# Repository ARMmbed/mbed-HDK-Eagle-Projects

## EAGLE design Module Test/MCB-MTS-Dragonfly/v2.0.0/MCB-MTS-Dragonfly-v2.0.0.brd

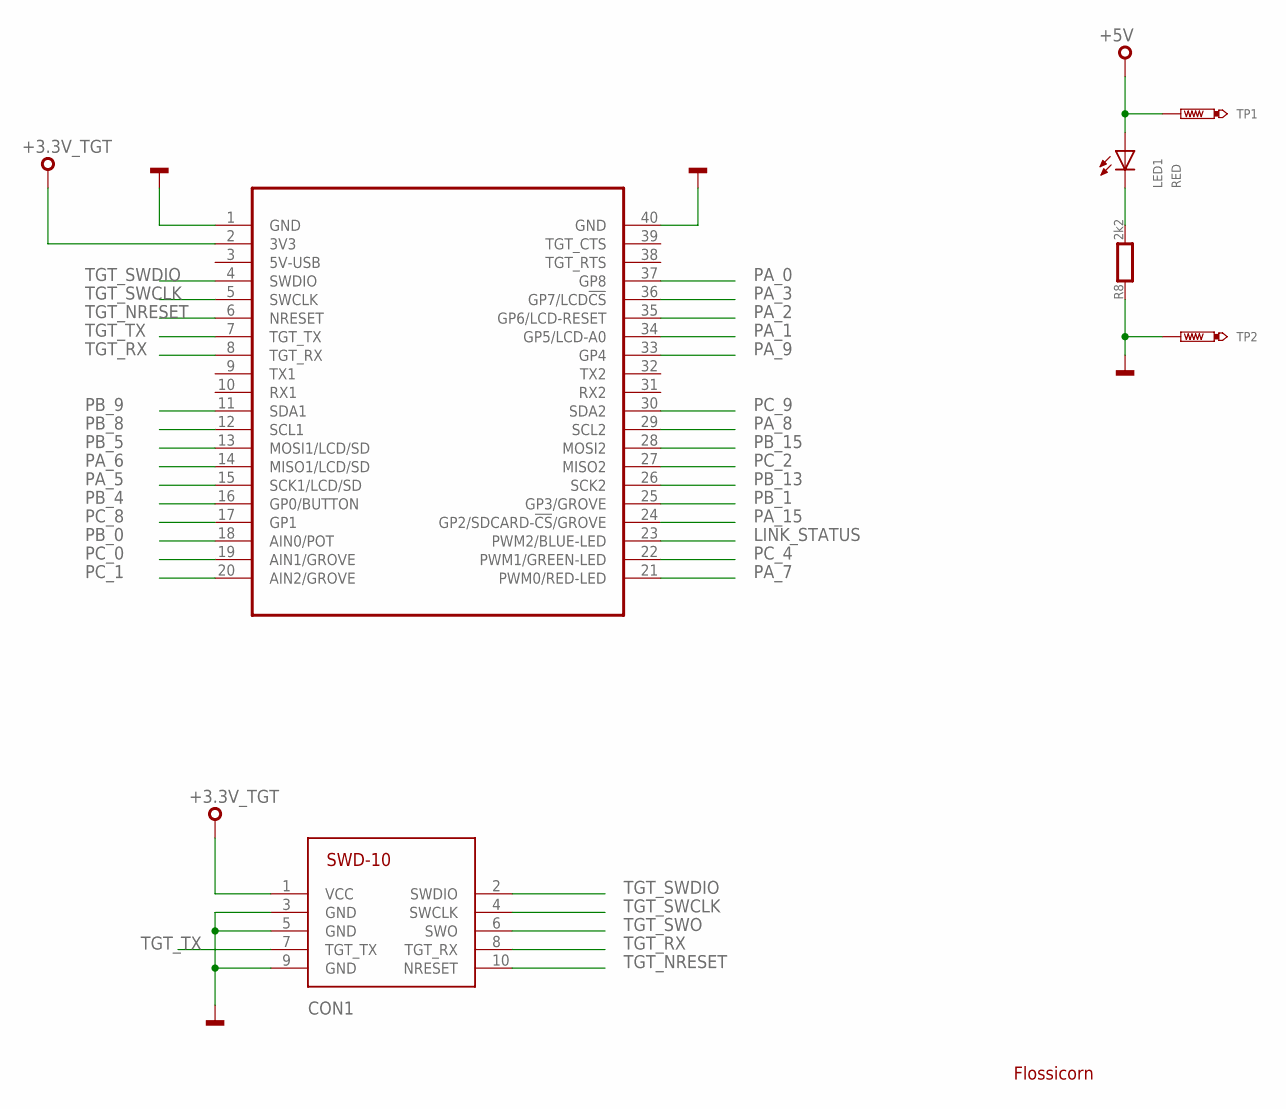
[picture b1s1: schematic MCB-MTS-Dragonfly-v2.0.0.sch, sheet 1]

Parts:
CON1: SWD-10/TC2050_SMD; FTSH-105-02
LED1: RED; CHIPLED_0603
MOD2: MODULE_DAUGHTER
R8: 2k2; 0603
SS1: FLOSSICORN0.5; FLOSSICORN-0.5
TP1, TP2: TEST-POINT-50R-PTH; TP50-PTH

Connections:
+3.3V_TGT: CON1.1 (VCC), MOD2.2 (3V3)
+5V: LED1.A, TP1.TP; also elsewhere on the board
GND: CON1.3 (GND), CON1.5 (GND), CON1.9 (GND), MOD2.1 (GND), MOD2.40 (GND), R8.1, TP2.TP; also elsewhere on the board
LINK_STATUS: MOD2.23 (PWM2/BLUE-LED); also elsewhere on the board
unnamed: LED1.C, R8.2
PA_0: MOD2.37 (GP8); also elsewhere on the board
PA_1: MOD2.34 (GP5/LCD-A0); also elsewhere on the board
PA_2: MOD2.35 (GP6/LCD-RESET); also elsewhere on the board
PA_3: MOD2.36 (GP7/LCD!CS); also elsewhere on the board
PA_5: MOD2.15 (SCK1/LCD/SD); also elsewhere on the board
PA_6: MOD2.14 (MISO1/LCD/SD); also elsewhere on the board
PA_7: MOD2.21 (PWM0/RED-LED); also elsewhere on the board
PA_8: MOD2.29 (SCL2); also elsewhere on the board
PA_9: MOD2.33 (GP4); also elsewhere on the board
PA_15: MOD2.24 (GP2/SDCARD-!CS!/GROVE); also elsewhere on the board
PB_0: MOD2.18 (AIN0/POT); also elsewhere on the board
PB_1: MOD2.25 (GP3/GROVE); also elsewhere on the board
PB_4: MOD2.16 (GP0/BUTTON); also elsewhere on the board
PB_5: MOD2.13 (MOSI1/LCD/SD); also elsewhere on the board
PB_8: MOD2.12 (SCL1); also elsewhere on the board
PB_9: MOD2.11 (SDA1); also elsewhere on the board
PB_13: MOD2.26 (SCK2); also elsewhere on the board
PB_15: MOD2.28 (MOSI2); also elsewhere on the board
PC_0: MOD2.19 (AIN1/GROVE); also elsewhere on the board
PC_1: MOD2.20 (AIN2/GROVE); also elsewhere on the board
PC_2: MOD2.27 (MISO2); also elsewhere on the board
PC_4: MOD2.22 (PWM1/GREEN-LED); also elsewhere on the board
PC_8: MOD2.17 (GP1); also elsewhere on the board
PC_9: MOD2.30 (SDA2); also elsewhere on the board
TGT_NRESET: CON1.10 (NRESET), MOD2.6 (NRESET); also elsewhere on the board
TGT_RX: CON1.8 (TGT_RX), MOD2.8 (TGT_RX); also elsewhere on the board
TGT_SWCLK: CON1.4 (SWCLK), MOD2.5 (SWCLK); also elsewhere on the board
TGT_SWDIO: CON1.2 (SWDIO), MOD2.4 (SWDIO); also elsewhere on the board
TGT_SWO: CON1.6 (SWO); also elsewhere on the board
TGT_TX: CON1.7 (TGT_TX), MOD2.7 (TGT_TX); also elsewhere on the board

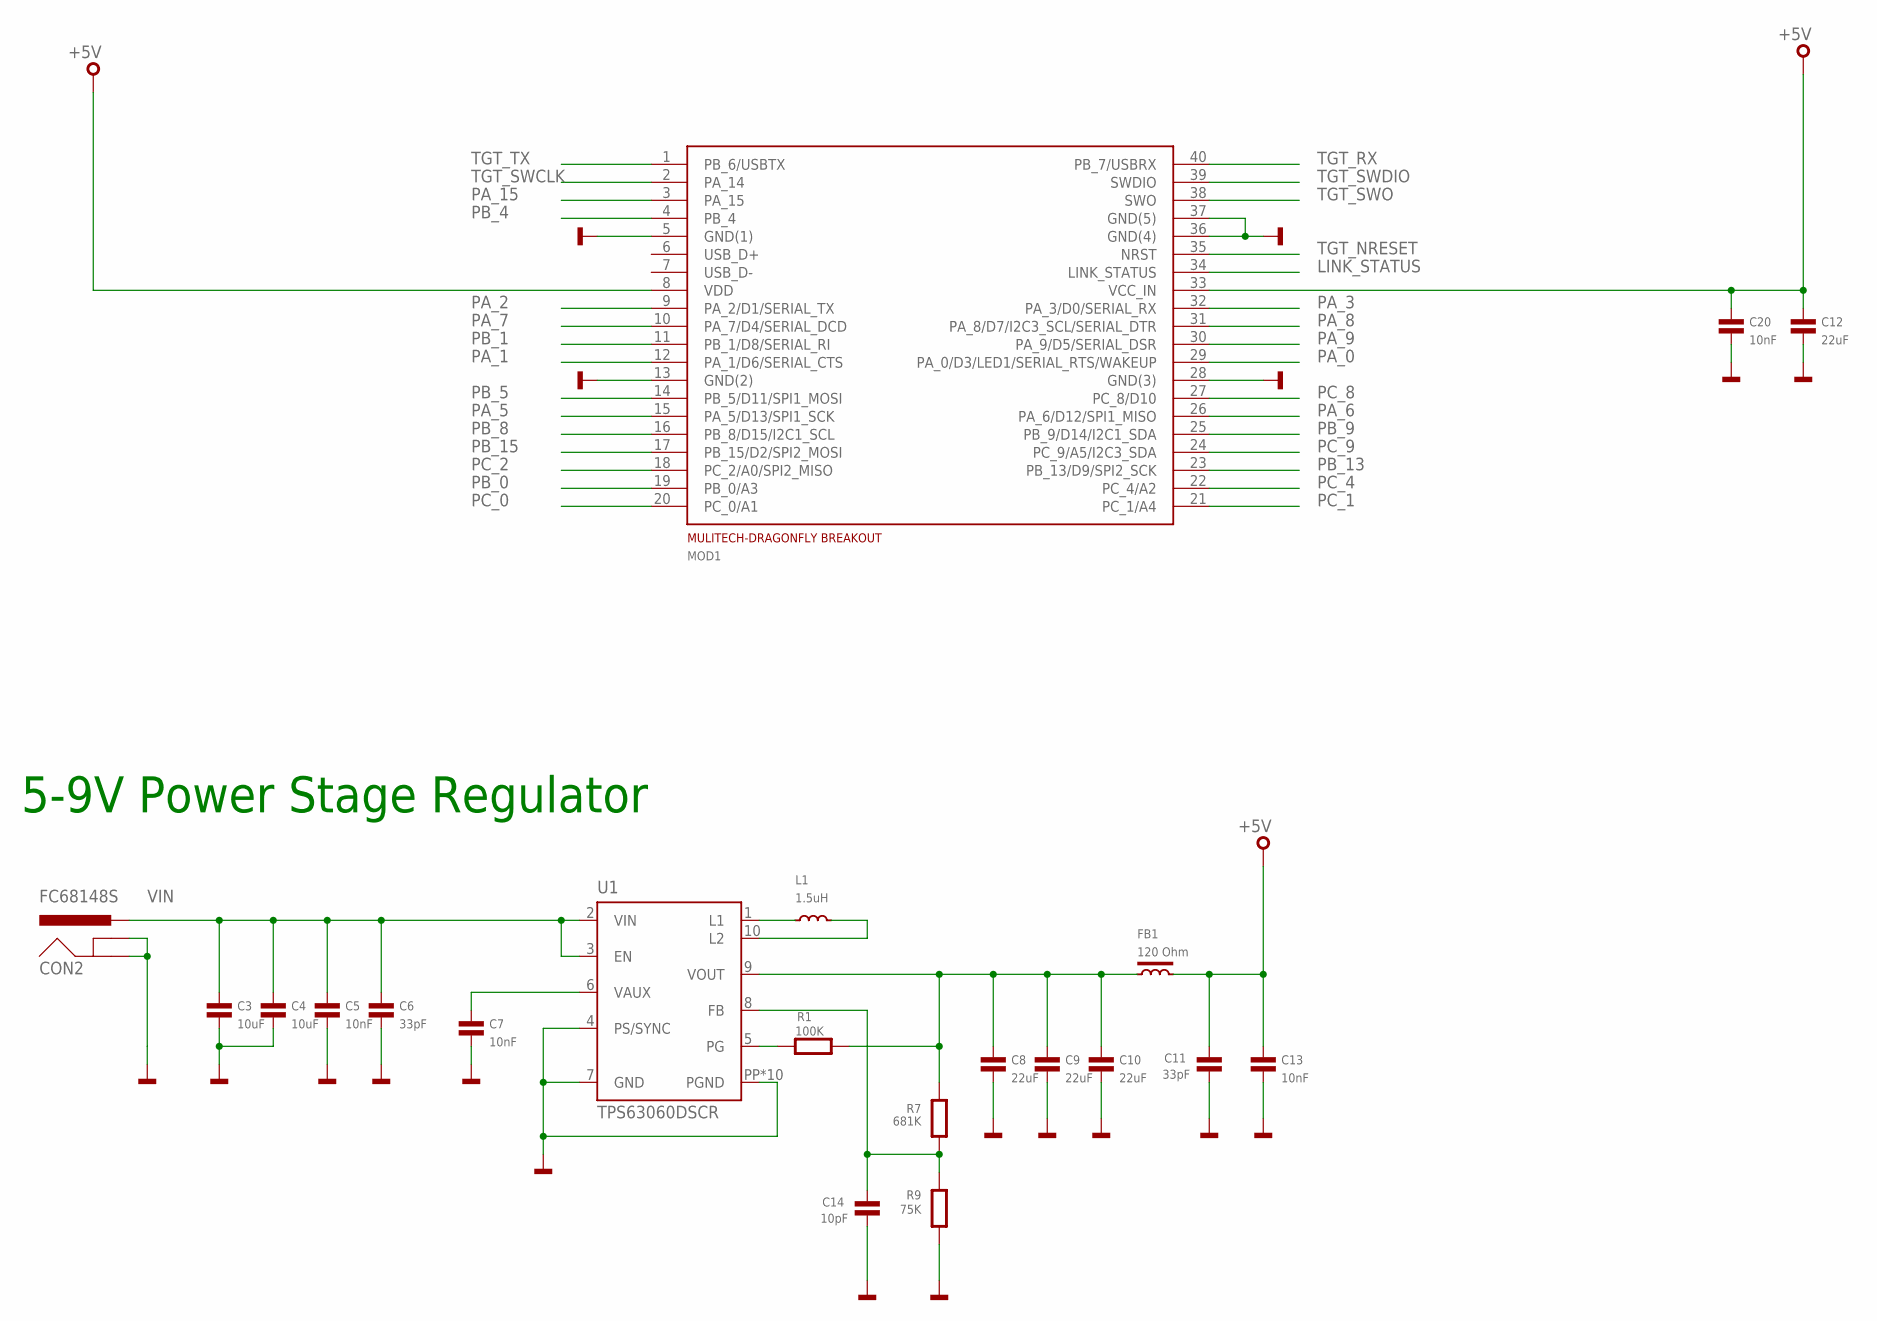
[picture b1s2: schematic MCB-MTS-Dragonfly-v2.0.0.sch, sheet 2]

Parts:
C3, C4: 10uF; 0603
C5, C7, C13, C20: 10nF; 0603
C6, C11: 33pF; 0603
C8, C9, C10, C12: 22uF; 0603
C14: 10pF; 0603
CON2: FC68148S
FB1: 120 Ohm; 0603
L1: 1.5uH; XFL4020-472MEC
MOD1: MULITECH-DRAGONFLY-BREAKOUT
R1: 100K; 0402
R7: 681K; 0402
R9: 75K; 0402
U1: TPS63060DSCR; DSC-S-PWSON-N10

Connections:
+5V: C11.1, C12.1, C13.1, C20.1, FB1.2, MOD1.8 (VDD), MOD1.33 (VCC_IN); also elsewhere on the board
GND: C3.2, C4.2, C5.2, C6.2, C7.2, C8.2, C9.2, C10.2, C11.2, C12.2, C13.2, C14.2, C20.2, CON2.2 (GNDBREAK), CON2.3 (GND), MOD1.5 (GND(1)), MOD1.13 (GND(2)), MOD1.28 (GND(3)), MOD1.36 (GND(4)), MOD1.37 (GND(5)), R9.1, U1.4 (PS/SYNC), U1.7 (GND), U1.PP (PGND), U1.PP@1 (PGND), U1.PP@2 (PGND), U1.PP@3 (PGND), U1.PP@4 (PGND), U1.PP@5 (PGND), U1.PP@7 (PGND), U1.PP@8 (PGND), U1.PP@9 (PGND), U1.PP@10 (PGND); also elsewhere on the board
LINK_STATUS: MOD1.34 (LINK_STATUS); also elsewhere on the board
unnamed: C7.1, U1.6 (VAUX)
unnamed: L1.P$1, U1.1 (L1)
unnamed: L1.P$2, U1.10 (L2)
unnamed: C14.1, R7.1, R9.2, U1.8 (FB)
unnamed: C8.1, C9.1, C10.1, FB1.1, R1.2, R7.2, U1.9 (VOUT)
unnamed: R1.1, U1.5 (PG)
PA_0: MOD1.29 (PA_0/D3/LED1/SERIAL_RTS/WAKEUP); also elsewhere on the board
PA_1: MOD1.12 (PA_1/D6/SERIAL_CTS); also elsewhere on the board
PA_2: MOD1.9 (PA_2/D1/SERIAL_TX); also elsewhere on the board
PA_3: MOD1.32 (PA_3/D0/SERIAL_RX); also elsewhere on the board
PA_5: MOD1.15 (PA_5/D13/SPI1_SCK); also elsewhere on the board
PA_6: MOD1.26 (PA_6/D12/SPI1_MISO); also elsewhere on the board
PA_7: MOD1.10 (PA_7/D4/SERIAL_DCD); also elsewhere on the board
PA_8: MOD1.31 (PA_8/D7/I2C3_SCL/SERIAL_DTR); also elsewhere on the board
PA_9: MOD1.30 (PA_9/D5/SERIAL_DSR); also elsewhere on the board
PA_15: MOD1.3 (PA_15); also elsewhere on the board
PB_0: MOD1.19 (PB_0/A3); also elsewhere on the board
PB_1: MOD1.11 (PB_1/D8/SERIAL_RI); also elsewhere on the board
PB_4: MOD1.4 (PB_4); also elsewhere on the board
PB_5: MOD1.14 (PB_5/D11/SPI1_MOSI); also elsewhere on the board
PB_8: MOD1.16 (PB_8/D15/I2C1_SCL); also elsewhere on the board
PB_9: MOD1.25 (PB_9/D14/I2C1_SDA); also elsewhere on the board
PB_13: MOD1.23 (PB_13/D9/SPI2_SCK); also elsewhere on the board
PB_15: MOD1.17 (PB_15/D2/SPI2_MOSI); also elsewhere on the board
PC_0: MOD1.20 (PC_0/A1); also elsewhere on the board
PC_1: MOD1.21 (PC_1/A4); also elsewhere on the board
PC_2: MOD1.18 (PC_2/A0/SPI2_MISO); also elsewhere on the board
PC_4: MOD1.22 (PC_4/A2); also elsewhere on the board
PC_8: MOD1.27 (PC_8/D10); also elsewhere on the board
PC_9: MOD1.24 (PC_9/A5/I2C3_SDA); also elsewhere on the board
TGT_NRESET: MOD1.35 (NRST); also elsewhere on the board
TGT_RX: MOD1.40 (PB_7/USBRX); also elsewhere on the board
TGT_SWCLK: MOD1.2 (PA_14); also elsewhere on the board
TGT_SWDIO: MOD1.39 (SWDIO); also elsewhere on the board
TGT_SWO: MOD1.38 (SWO); also elsewhere on the board
TGT_TX: MOD1.1 (PB_6/USBTX); also elsewhere on the board
VIN: C3.1, C4.1, C5.1, C6.1, CON2.1-1 (PWR), CON2.1-2 (PWR), U1.2 (VIN), U1.3 (EN)

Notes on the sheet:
5-9V Power Stage Regulator

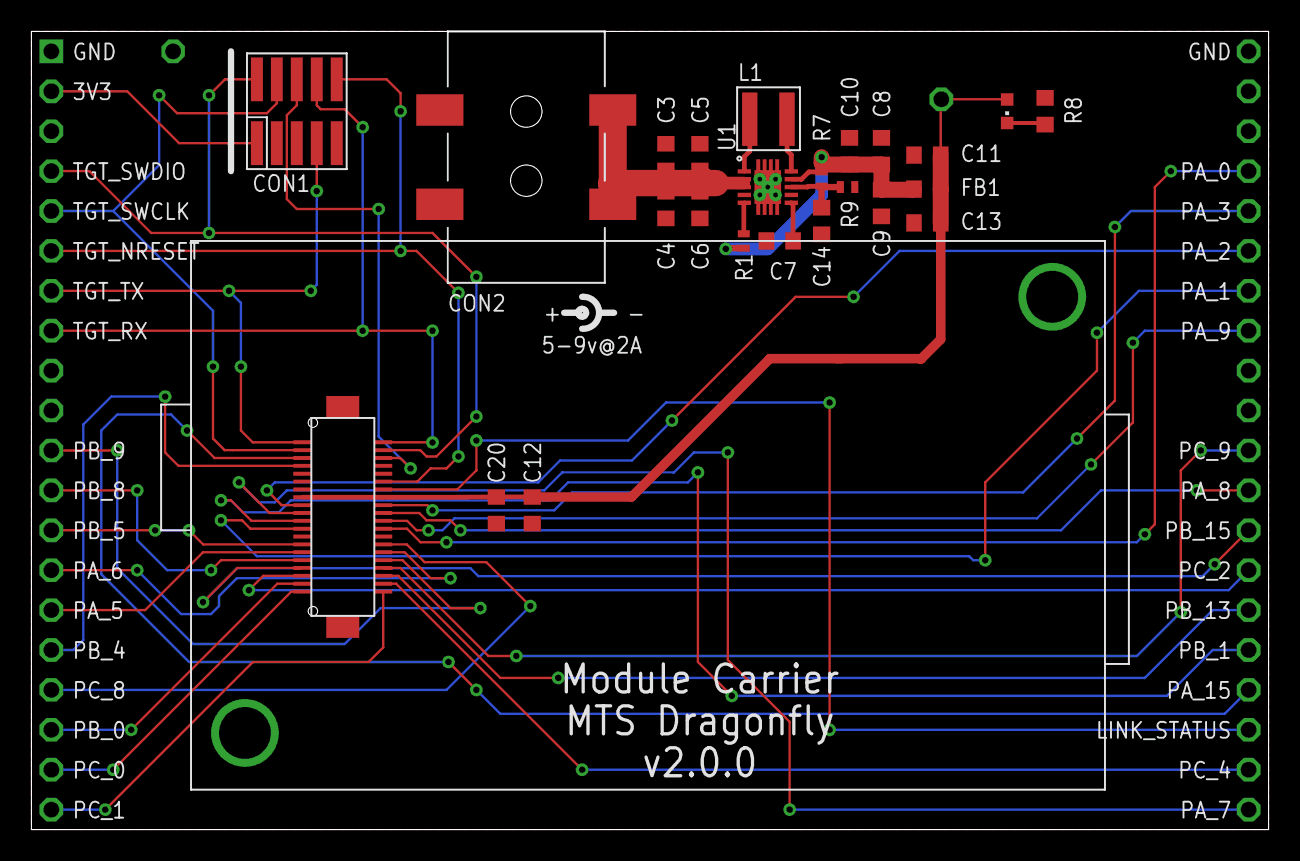
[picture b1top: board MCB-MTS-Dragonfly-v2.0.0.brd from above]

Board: 2 copper layers, 78.7 x 50.8 mm, 28 parts (0 on the bottom side), 42 nets.

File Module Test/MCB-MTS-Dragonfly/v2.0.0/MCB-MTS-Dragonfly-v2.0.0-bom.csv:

"Qty";"Value";"Device";"Package";"Parts";"Description";"MF";"MFN";"OC-DIGIKEY";"OC-MOUSER";"OC-NEWARK";
"1";"1.5uH";"INDUCTORXFL4020";"XFL4020-472MEC";"L1";"Inductor";"";"";"";"";"";
"1";"100K";"RESISTOR0402";"0402";"R1";"Resistor";"";"";"";"";"";
"4";"10nF";"CAPACITOR0603";"0603";"C5, C7, C13, C20";"Capacitor";"";"";"";"";"";
"1";"10pF";"CAPACITOR0603";"0603";"C14";"Capacitor";"";"";"";"";"";
"2";"10uF";"CAPACITOR0603";"0603";"C3, C4";"Capacitor";"";"";"";"";"";
"1";"120 Ohm";"FERRITE0603";"0603";"FB1";"Ferrite Bead";"";"";"";"";"";
"4";"22uF";"CAPACITOR0603";"0603";"C8, C9, C10, C12";"Capacitor";"";"";"";"";"";
"1";"2k2";"RESISTOR0603";"0603";"R8";"Resistor";"";"";"";"";"";
"2";"33pF";"CAPACITOR0603";"0603";"C6, C11";"Capacitor";"";"";"";"";"";
"1";"681K";"RESISTOR0402";"0402";"R7";"Resistor";"";"";"";"";"";
"1";"75K";"RESISTOR0402";"0402";"R9";"Resistor";"";"";"";"";"";
"1";"FC68148S";"FC68148S";"FC68148S";"CON2";"Power Jack";"";"";"";"";"";
"1";"FLOSSICORN0.5";"FLOSSICORN0.5";"FLOSSICORN-0.5";"SS1";"";"";"";"";"";"";
"1";"MODULE_DAUGHTER";"MODULE_DAUGHTER";"MODULE_DAUGHTER";"MOD2";"";"";"";"";"";"";
"1";"MULITECH-DRAGONFLY-BREAKOUT";"MULITECH-DRAGONFLY-BREAKOUT";"MULITECH-DRAGONFLY-BREAKOUT";"MOD1";"Breakout for Multitech Dragonfly";"Hirose";"DF17(2.0)-40DP-0.5V(57)";"H11130CT-ND";"798-DF172040DP05V57";"2300341";
"1";"RED";"SMD_LED0603";"CHIPLED_0603";"LED1";"LED SMD, Colour Red";"Wurth Electronics Inc";"150060RS75000";"732-4978-1-ND";"710-150060RS75000";"2322071";
"1";"SWD-10/TC2050_SMD";"SWD-10/TC2050_SMD";"FTSH-105-02";"CON1";"1mm pitch 10-Pin Cortex Programming Header with optional TC2050 footprint solderless interchangeable";"";"";"";"";"";
"2";"TEST-POINT-50R-PTH";"TEST-POINT-50R-PTH";"TP50-PTH";"TP1, TP2";"";"";"";"";"";"";
"1";"TPS63060DSCR";"TPS63060DSCR";"DSC-S-PWSON-N10";"U1";"Buck Boost Conveter (2.5V-12Vin, 2.5V-8Vout, 2Aout)";"TEXAS INSTRUMENTS";"TPS63060DSCR";"296-30204-1-ND";"595-TPS63060DSCR";"76T8143";

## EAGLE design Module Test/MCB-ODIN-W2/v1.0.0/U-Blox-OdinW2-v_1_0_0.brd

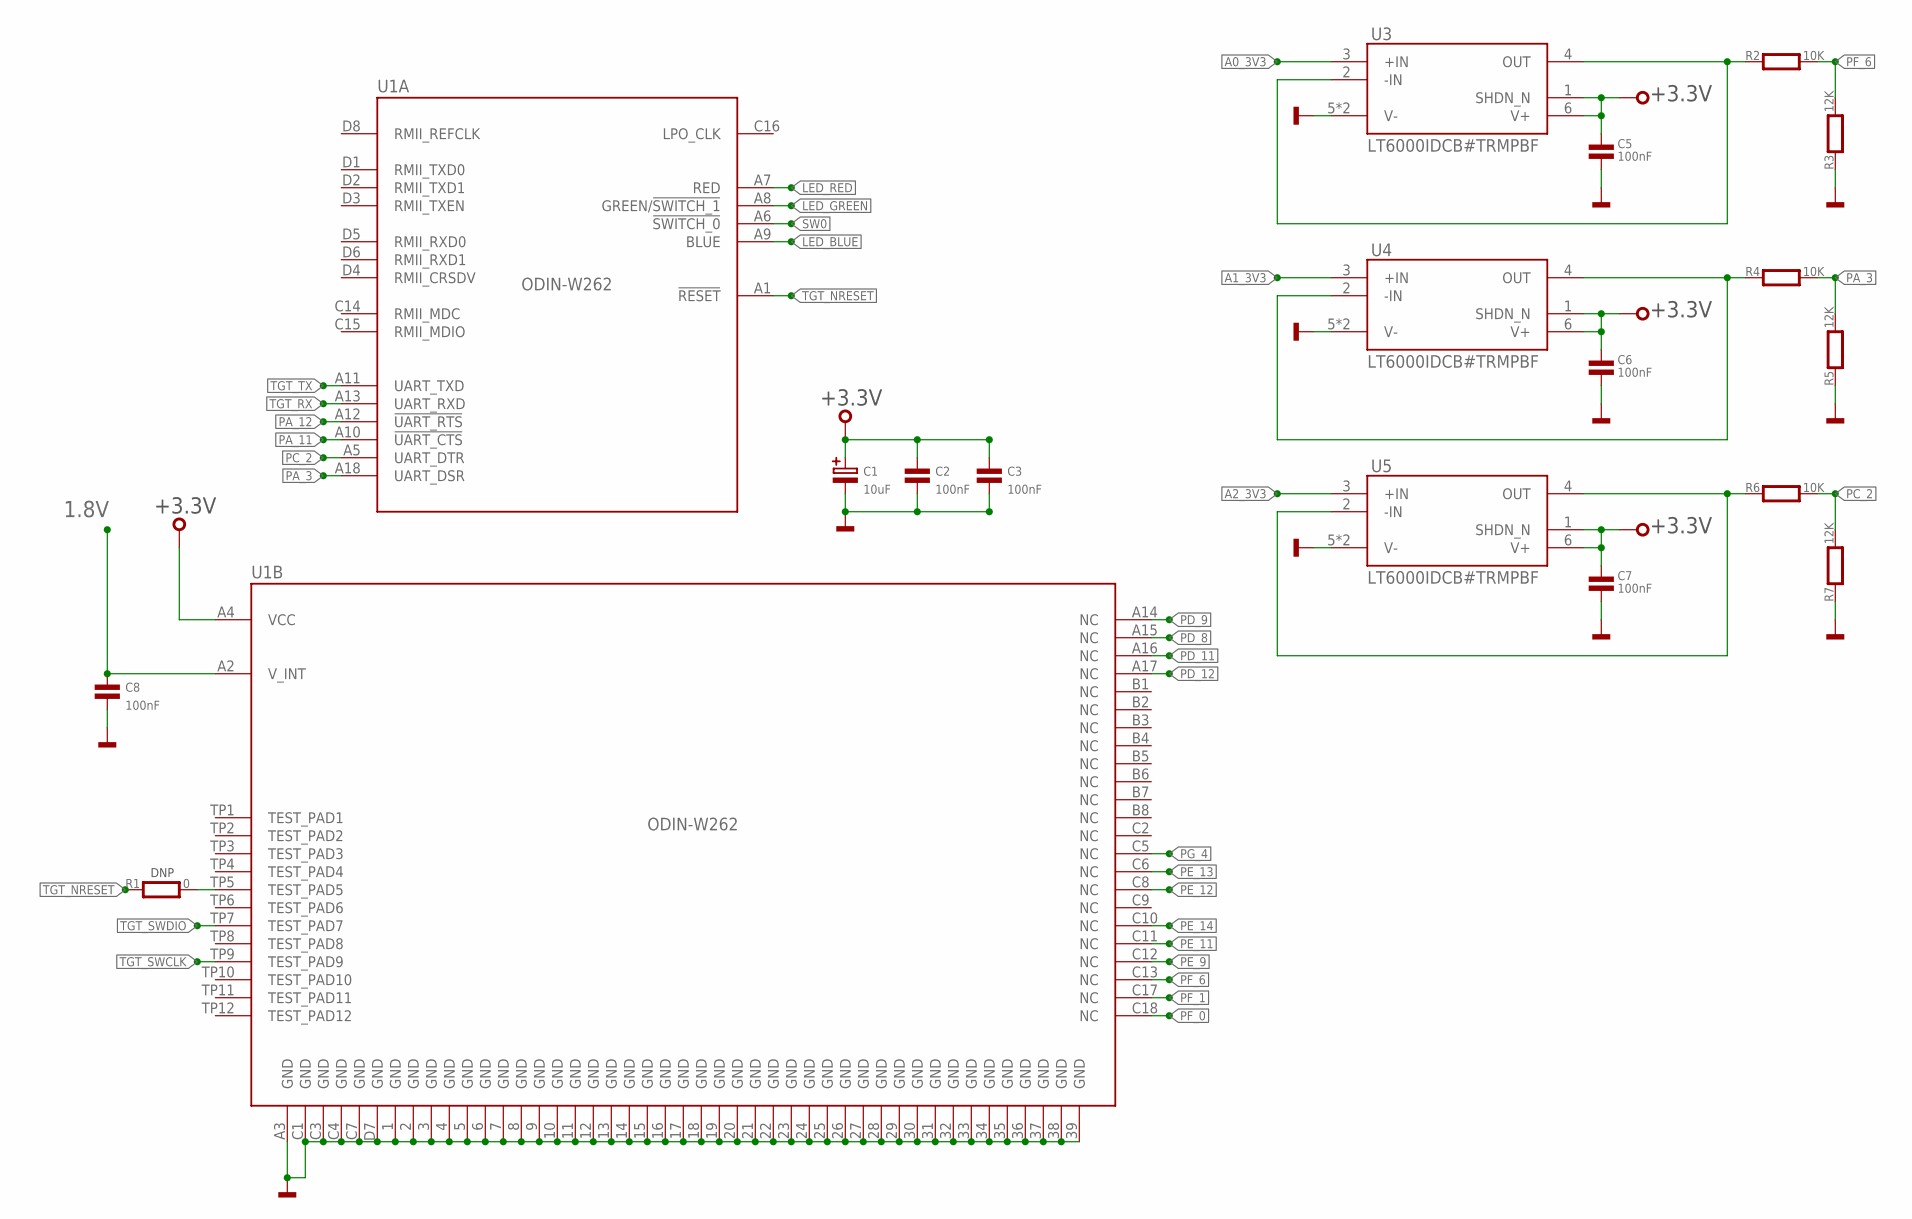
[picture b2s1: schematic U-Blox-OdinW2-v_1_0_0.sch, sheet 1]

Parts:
C1: 10uF; SMC_B
C2, C3, C5, C6, C7, C8: 100nF; 0603
R1: 0; 0402
R2, R4, R6: 10K; 0402
R3, R5, R7: 12K; 0402
U1: ODIN-W262; ODIN-88
U3, U4, U5: LT6000IDCB#TRMPBF; 6-DFN

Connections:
1.8V: C8.1, U1.A2 (V_INT); also elsewhere on the board
+3.3V: C1.+, C2.1, C3.1, C5.1, C6.1, C7.1, U1.A4 (VCC), U3.1 (SHDN_N), U3.6 (V+), U4.1 (SHDN_N), U4.6 (V+), U5.1 (SHDN_N), U5.6 (V+); also elsewhere on the board
A0_3V3: U3.3 (+IN); also elsewhere on the board
A1_3V3: U4.3 (+IN); also elsewhere on the board
A2_3V3: U5.3 (+IN); also elsewhere on the board
GND: C1.-, C2.2, C3.2, C5.2, C6.2, C7.2, C8.2, R3.1, R5.1, R7.1, U1.1 (GND), U1.2 (GND), U1.3 (GND), U1.4 (GND), U1.5 (GND), U1.6 (GND), U1.7 (GND), U1.8 (GND), U1.9 (GND), U1.10 (GND), U1.11 (GND), U1.12 (GND), U1.13 (GND), U1.14 (GND), U1.15 (GND), U1.16 (GND), U1.17 (GND), U1.18 (GND), U1.19 (GND), U1.20 (GND), U1.21 (GND), U1.22 (GND), U1.23 (GND), U1.24 (GND), U1.25 (GND), U1.26 (GND), U1.27 (GND), U1.28 (GND), U1.29 (GND), U1.30 (GND), U1.31 (GND), U1.32 (GND), U1.33 (GND), U1.34 (GND), U1.35 (GND), U1.36 (GND), U1.37 (GND), U1.38 (GND), U1.39 (GND), U1.A3 (GND), U1.C1 (GND), U1.C3 (GND), U1.C4 (GND), U1.C7 (GND), U1.D7 (GND), U3.5 (V-), U3.P$7 (V-), U4.5 (V-), U4.P$7 (V-), U5.5 (V-), U5.P$7 (V-); also elsewhere on the board
LED_BLUE: U1.A9 (BLUE); also elsewhere on the board
LED_GREEN: U1.A8 (GREEN/!SWITCH_1); also elsewhere on the board
LED_RED: U1.A7 (RED); also elsewhere on the board
unnamed: R1.2, U1.TP5 (TEST_PAD5)
unnamed: R2.1, U3.2 (-IN), U3.4 (OUT)
unnamed: R4.1, U4.2 (-IN), U4.4 (OUT)
unnamed: R6.1, U5.2 (-IN), U5.4 (OUT)
PA_3: R4.2, R5.2, U1.A18 (UART_DSR)
PA_11: U1.A10 (!UART_CTS); also elsewhere on the board
PA_12: U1.A12 (!UART_RTS); also elsewhere on the board
PC_2: R6.2, R7.2, U1.A5 (UART_DTR)
PD_8: U1.A15 (NC); also elsewhere on the board
PD_9: U1.A14 (NC); also elsewhere on the board
PD_11: U1.A16 (NC); also elsewhere on the board
PD_12: U1.A17 (NC); also elsewhere on the board
PE_9: U1.C12 (NC); also elsewhere on the board
PE_11: U1.C11 (NC); also elsewhere on the board
PE_12: U1.C8 (NC); also elsewhere on the board
PE_13: U1.C6 (NC); also elsewhere on the board
PE_14: U1.C10 (NC); also elsewhere on the board
PF_0: U1.C18 (NC); also elsewhere on the board
PF_1: U1.C17 (NC); also elsewhere on the board
PF_6: R2.2, R3.2, U1.C13 (NC)
PG_4: U1.C5 (NC); also elsewhere on the board
SW0: U1.A6 (!SWITCH_0); also elsewhere on the board
TGT_NRESET: R1.1, U1.A1 (!RESET); also elsewhere on the board
TGT_RX: U1.A13 (UART_RXD); also elsewhere on the board
TGT_SWCLK: U1.TP9 (TEST_PAD9); also elsewhere on the board
TGT_SWDIO: U1.TP7 (TEST_PAD7); also elsewhere on the board
TGT_TX: U1.A11 (UART_TXD); also elsewhere on the board

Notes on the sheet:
DNP

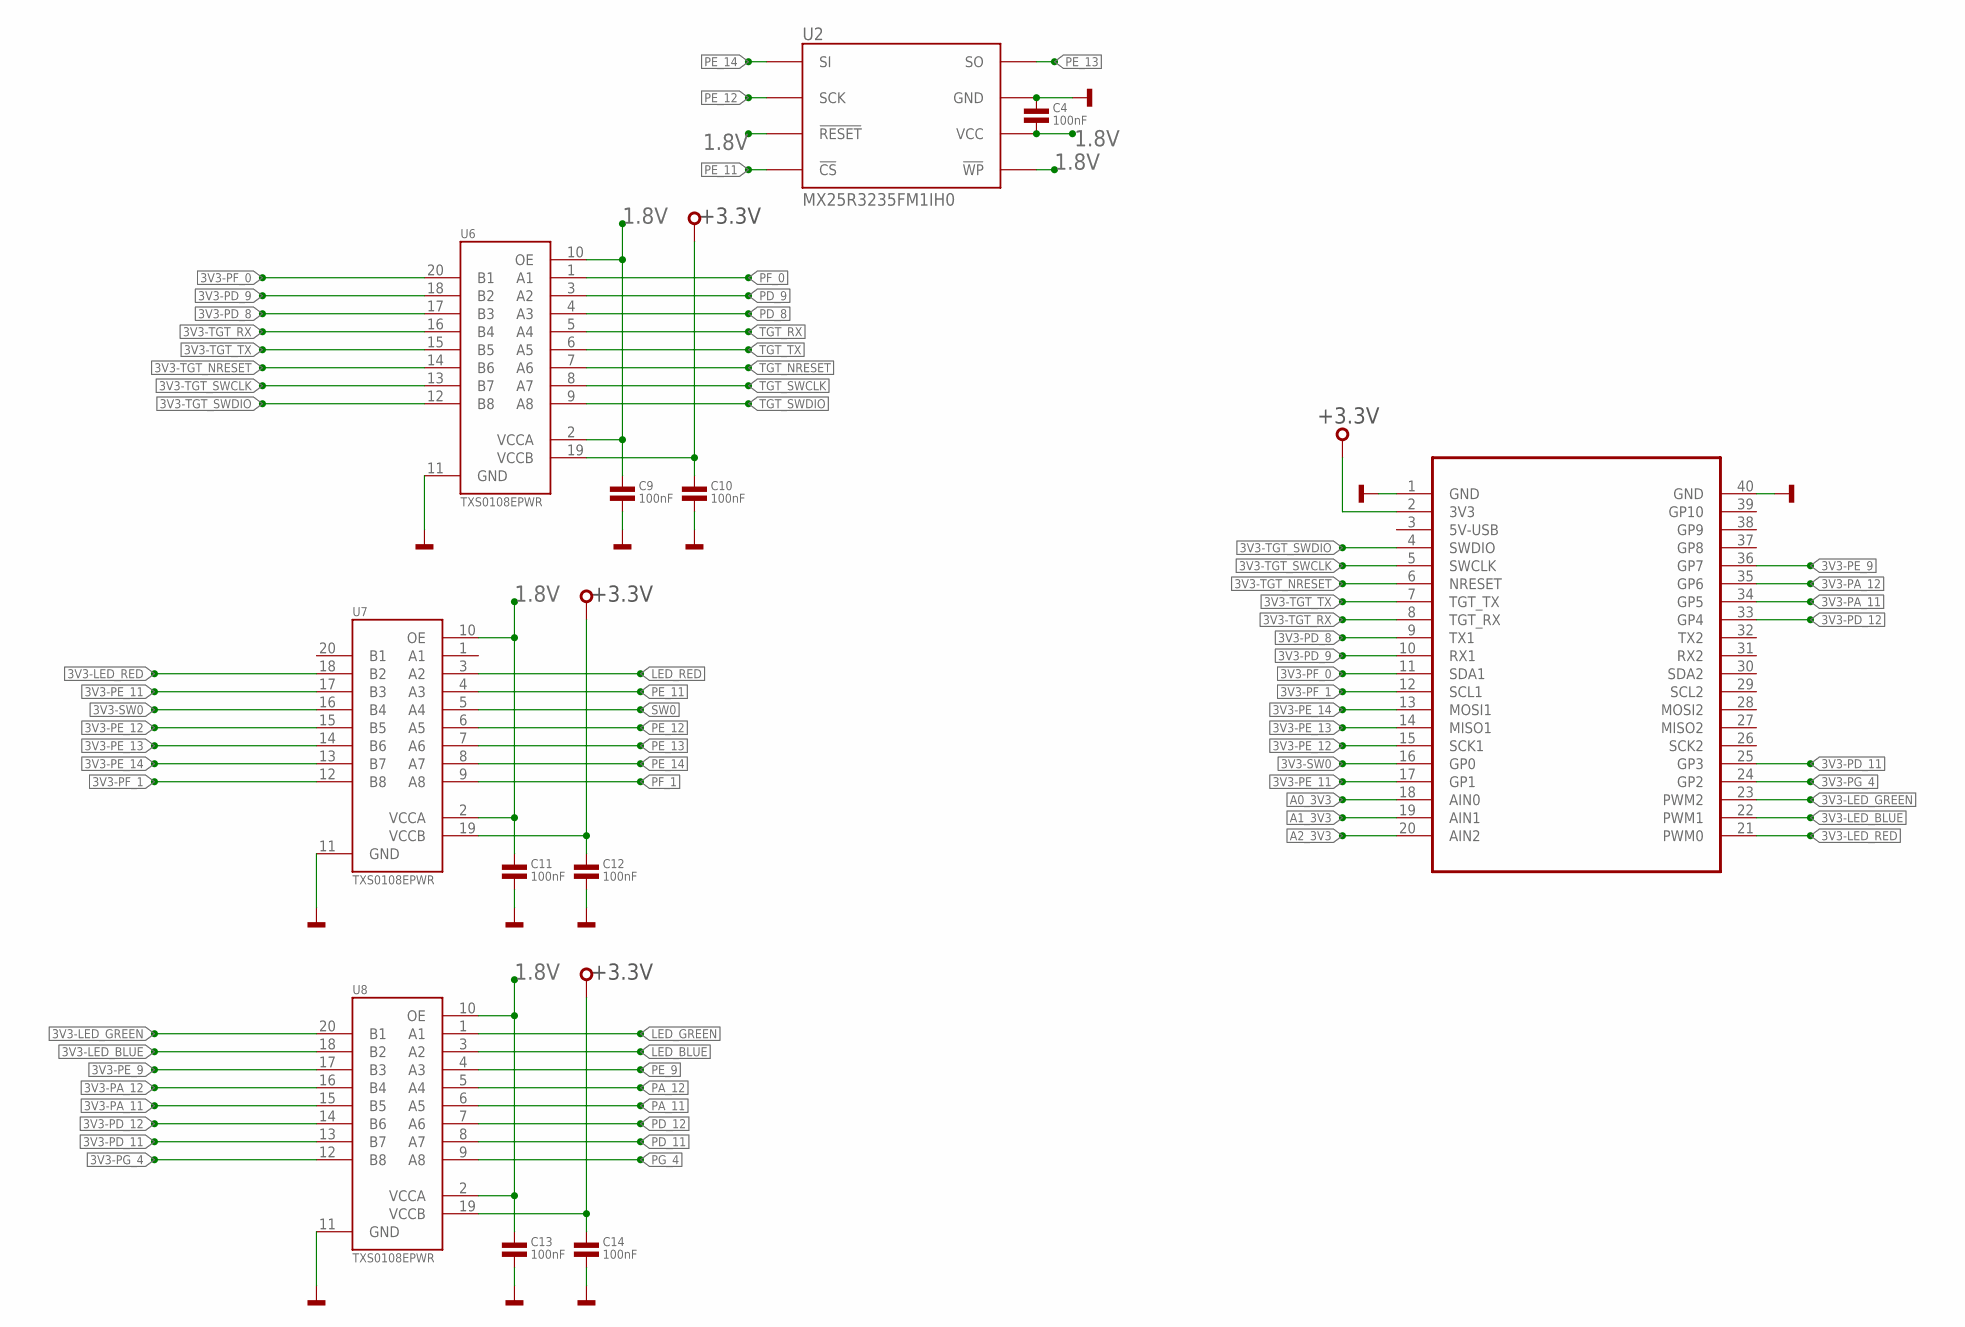
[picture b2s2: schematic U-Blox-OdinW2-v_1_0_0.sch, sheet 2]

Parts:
C4, C9, C10, C11, C12, C13, C14: 100nF; 0603
U2: MX25R3235FM1IH0; SO8
U6, U7, U8: TXS0108EPWR; TSSOP-20
U$1: MODULE_DAUGHTER

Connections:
1.8V: C4.2, C9.1, C11.1, C13.1, U2.3 (!WP), U2.7 (!RESET), U2.8 (VCC), U6.2 (VCCA), U6.10 (OE), U7.2 (VCCA), U7.10 (OE), U8.2 (VCCA), U8.10 (OE); also elsewhere on the board
3V3-LED_BLUE: U8.18 (B2), U$1.22 (PWM1)
3V3-LED_GREEN: U8.20 (B1), U$1.23 (PWM2)
3V3-LED_RED: U7.18 (B2), U$1.21 (PWM0)
3V3-PA_11: U8.15 (B5), U$1.34 (GP5)
3V3-PA_12: U8.16 (B4), U$1.35 (GP6)
3V3-PD_8: U6.17 (B3), U$1.9 (TX1)
3V3-PD_9: U6.18 (B2), U$1.10 (RX1)
3V3-PD_11: U8.13 (B7), U$1.25 (GP3)
3V3-PD_12: U8.14 (B6), U$1.33 (GP4)
3V3-PE_9: U8.17 (B3), U$1.36 (GP7)
3V3-PE_11: U7.17 (B3), U$1.17 (GP1)
3V3-PE_12: U7.15 (B5), U$1.15 (SCK1)
3V3-PE_13: U7.14 (B6), U$1.14 (MISO1)
3V3-PE_14: U7.13 (B7), U$1.13 (MOSI1)
3V3-PF_0: U6.20 (B1), U$1.11 (SDA1)
3V3-PF_1: U7.12 (B8), U$1.12 (SCL1)
3V3-PG_4: U8.12 (B8), U$1.24 (GP2)
3V3-SW0: U7.16 (B4), U$1.16 (GP0)
3V3-TGT_NRESET: U6.14 (B6), U$1.6 (NRESET)
3V3-TGT_RX: U6.16 (B4), U$1.8 (TGT_RX)
3V3-TGT_SWCLK: U6.13 (B7), U$1.5 (SWCLK)
3V3-TGT_SWDIO: U6.12 (B8), U$1.4 (SWDIO)
3V3-TGT_TX: U6.15 (B5), U$1.7 (TGT_TX)
+3.3V: C10.1, C12.1, C14.1, U6.19 (VCCB), U7.19 (VCCB), U8.19 (VCCB), U$1.2 (3V3); also elsewhere on the board
A0_3V3: U$1.18 (AIN0); also elsewhere on the board
A1_3V3: U$1.19 (AIN1); also elsewhere on the board
A2_3V3: U$1.20 (AIN2); also elsewhere on the board
GND: C4.1, C9.2, C10.2, C11.2, C12.2, C13.2, C14.2, U2.4 (GND), U6.11 (GND), U7.11 (GND), U8.11 (GND), U$1.1 (GND), U$1.40 (GND); also elsewhere on the board
LED_BLUE: U8.3 (A2); also elsewhere on the board
LED_GREEN: U8.1 (A1); also elsewhere on the board
LED_RED: U7.3 (A2); also elsewhere on the board
PA_11: U8.6 (A5); also elsewhere on the board
PA_12: U8.5 (A4); also elsewhere on the board
PD_8: U6.4 (A3); also elsewhere on the board
PD_9: U6.3 (A2); also elsewhere on the board
PD_11: U8.8 (A7); also elsewhere on the board
PD_12: U8.7 (A6); also elsewhere on the board
PE_9: U8.4 (A3); also elsewhere on the board
PE_11: U2.1 (!CS), U7.4 (A3); also elsewhere on the board
PE_12: U2.6 (SCK), U7.6 (A5); also elsewhere on the board
PE_13: U2.2 (SO), U7.7 (A6); also elsewhere on the board
PE_14: U2.5 (SI), U7.8 (A7); also elsewhere on the board
PF_0: U6.1 (A1); also elsewhere on the board
PF_1: U7.9 (A8); also elsewhere on the board
PG_4: U8.9 (A8); also elsewhere on the board
SW0: U7.5 (A4); also elsewhere on the board
TGT_NRESET: U6.7 (A6); also elsewhere on the board
TGT_RX: U6.5 (A4); also elsewhere on the board
TGT_SWCLK: U6.8 (A7); also elsewhere on the board
TGT_SWDIO: U6.9 (A8); also elsewhere on the board
TGT_TX: U6.6 (A5); also elsewhere on the board

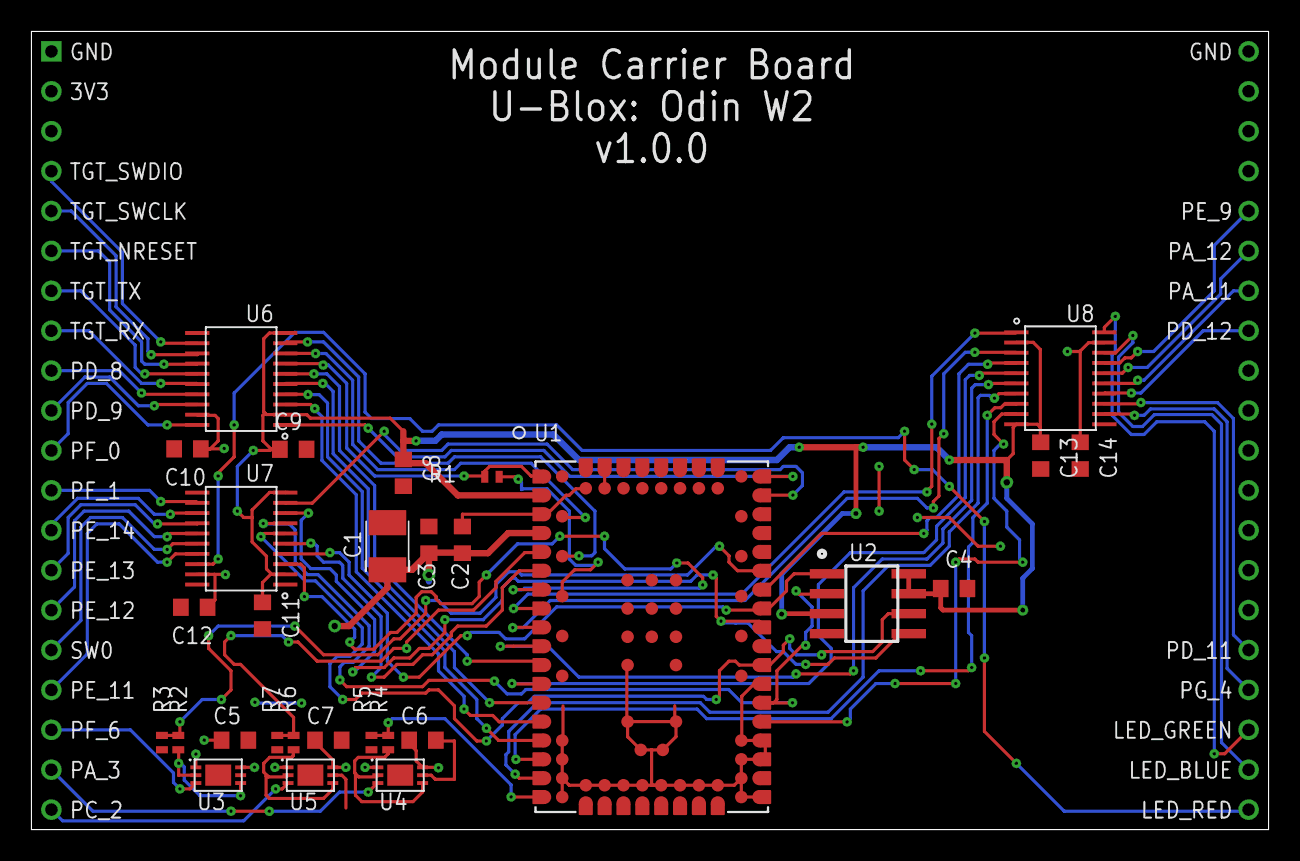
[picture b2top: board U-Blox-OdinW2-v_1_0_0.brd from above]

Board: 2 copper layers, 78.7 x 50.8 mm, 30 parts (0 on the bottom side), 59 nets.

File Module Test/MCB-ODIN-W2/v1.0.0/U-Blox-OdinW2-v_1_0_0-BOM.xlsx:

Qty | Value | Device | Package | Parts | Description | MF | MFN | OC-DIGIKEY | OC-MOUSER | OC-NEWARK
1 | 0 | RESISTOR0402 | 402 | R1 | Resistor | Yageo | RC0402JR-070RL | 311-0.0JRCT-ND | 603-RC0402JR-070RL | 603-RC0402JR-070RL
13 | 100nF | CAPACITOR0603 | 603 | C2, C3, C4, C5, C6, C7, C8, C9, C10, C11, C12, C13, C14 | Capacitor | AVX | 0603YC104KAT2A | 478-1239-1-ND | 581-060316C104K | 1327679
3 | 10K | RESISTOR0402 | 402 | R2, R4, R6 | Resistor | Vishay | CRCW040210K0JNED | 541-10KJCT-ND | 71-CRCW0402J-10K-E3 | 59M6696
1 | 10uF | CAPACITOR-POLARISEDB | SMC_B | C1 | Polarised capacitor | Kemet | T491B106K020AT | 399-8298-1-ND | 80-T491B106K020 | 57K1740
3 | 12K | RESISTOR0402 | 402 | R3, R5, R7 | Resistor | Panasonic | ERJ-2RKF1202X | P12.0KLCT-ND | 667-ERJ-2RKF1202X | 2302746
1 | 74LVC3G07DP,125 | 74LVC3G07DP,125 | TSSOP8 | U9 | IC BUFFER TRPL OP/DRAIN 8TSSOP | NXP | 74LVC3G07DP,125 | 1727-6684-1-ND | 771-74LVC3G07DP-G | 71R3483
1 | MX25R3235FM1IH0 | MX25R3235FM1IH0 | SO8 | U2 | Serial Flash 32 Mb 80 Mhz | Macronix | MX25R3235FM2IH0 | 1092-1174-ND
3 | LT6000IDCB#TRMPBF | LT6000IDCB#TRMPBF | 6-DFN | U3, U4, U5 | IC OPAMP GBP 60KHZ RRO 6DFN | Linear Technology | LT6000IDCB#TRMPBF | LT6000IDCB#TRMPBFCT-ND |  | 95M6567
1 | ODIN-W262 | ODIN-W262 | ODIN-88 | U1 | ODIN-W260: Host-based multiradio module with | U-Blox America Inc. | ODIN-W262 | 672-1017-1-ND
3 | TXS0108EPWR | TXS0108EPWR | TSSOP-20 | U6, U7, U8 | 8-Bit Bi-directional, Level-Shifting, Voltage Translator | Texas Instruments | TXS0108EPWR | 296-23011-1-ND | 595-TXS0108EPWR | 05R8300

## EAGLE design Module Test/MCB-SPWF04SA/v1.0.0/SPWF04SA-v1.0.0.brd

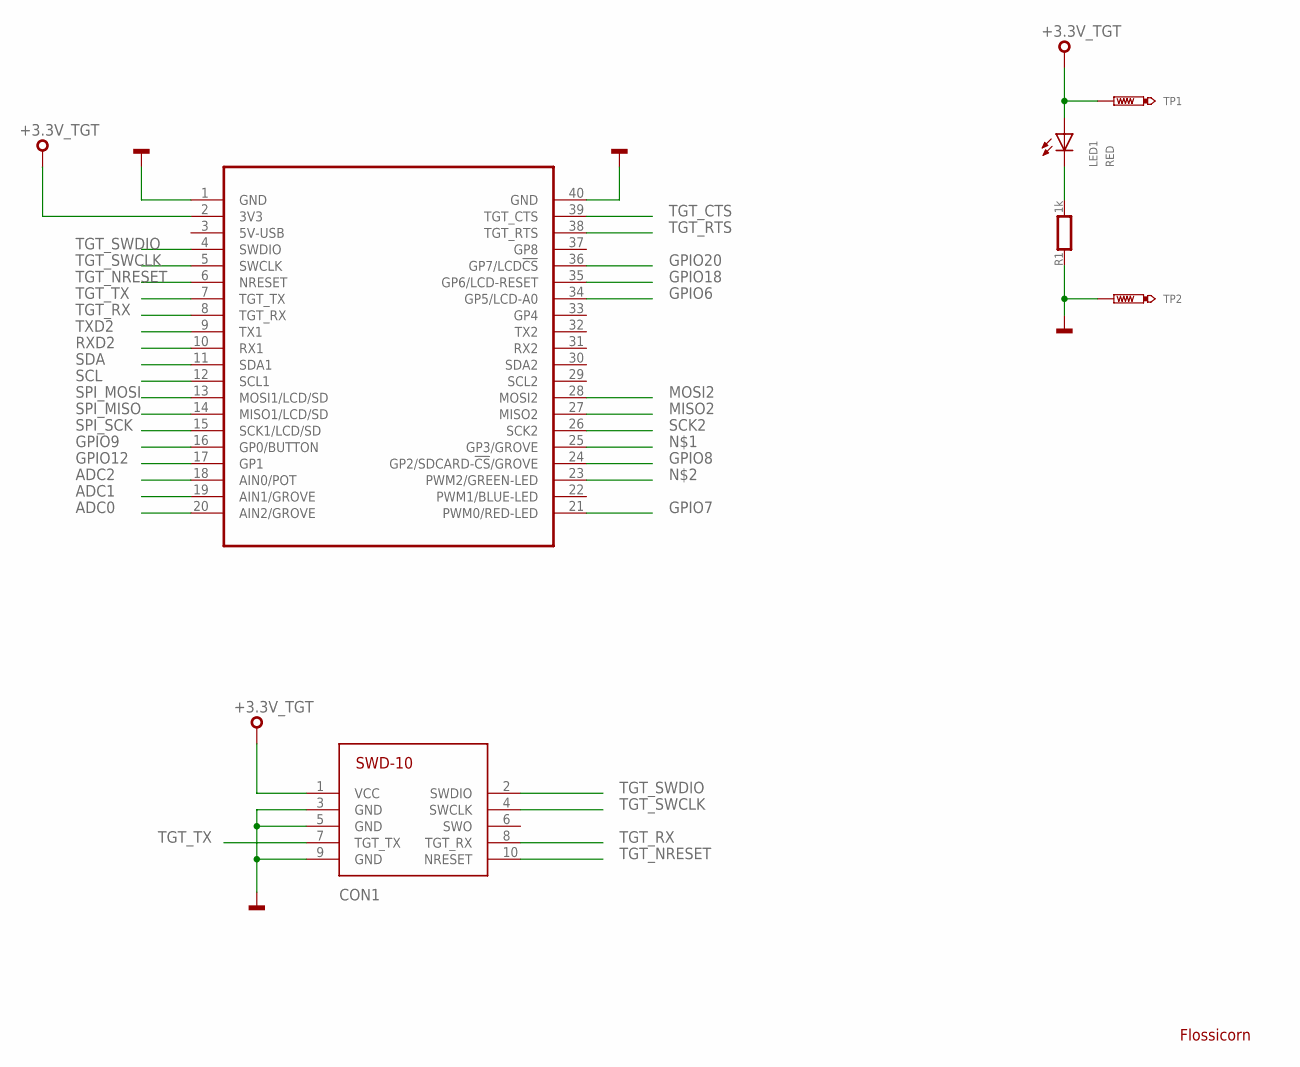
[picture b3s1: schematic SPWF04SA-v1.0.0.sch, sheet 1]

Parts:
CON1: SWD-10/TC2050_SMD; FTSH-105-02
LED1: RED; CHIPLED_0603
MOD1: MODULE_DAUGHTER
R1: 1k; 0603
SS1: FLOSSICORN0.5; FLOSSICORN-0.5
TP1, TP2: TEST-POINT-50R-PTH; TP50-PTH

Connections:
+3.3V_TGT: CON1.1 (VCC), LED1.A, MOD1.2 (3V3), TP1.TP; also elsewhere on the board
ADC0: MOD1.20 (AIN2/GROVE); also elsewhere on the board
ADC1: MOD1.19 (AIN1/GROVE); also elsewhere on the board
ADC2: MOD1.18 (AIN0/POT); also elsewhere on the board
GND: CON1.3 (GND), CON1.5 (GND), CON1.9 (GND), MOD1.1 (GND), MOD1.40 (GND), R1.1, TP2.TP; also elsewhere on the board
GPIO6: MOD1.34 (GP5/LCD-A0); also elsewhere on the board
GPIO7: MOD1.21 (PWM0/RED-LED); also elsewhere on the board
GPIO8: MOD1.24 (GP2/SDCARD-!CS!/GROVE); also elsewhere on the board
GPIO9: MOD1.16 (GP0/BUTTON); also elsewhere on the board
GPIO12: MOD1.17 (GP1); also elsewhere on the board
GPIO18: MOD1.35 (GP6/LCD-RESET); also elsewhere on the board
GPIO20: MOD1.36 (GP7/LCD!CS); also elsewhere on the board
MISO2: MOD1.27 (MISO2); also elsewhere on the board
MOSI2: MOD1.28 (MOSI2); also elsewhere on the board
PA_1: LED1.C, R1.2
RXD2: MOD1.10 (RX1); also elsewhere on the board
SCK2: MOD1.26 (SCK2); also elsewhere on the board
SCL: MOD1.12 (SCL1); also elsewhere on the board
SDA: MOD1.11 (SDA1); also elsewhere on the board
SPI_MISO: MOD1.14 (MISO1/LCD/SD); also elsewhere on the board
SPI_MOSI: MOD1.13 (MOSI1/LCD/SD); also elsewhere on the board
SPI_SCK: MOD1.15 (SCK1/LCD/SD); also elsewhere on the board
TGT_CTS: MOD1.39 (TGT_CTS); also elsewhere on the board
TGT_NRESET: CON1.10 (NRESET), MOD1.6 (NRESET); also elsewhere on the board
TGT_RTS: MOD1.38 (TGT_RTS); also elsewhere on the board
TGT_RX: CON1.8 (TGT_RX), MOD1.8 (TGT_RX); also elsewhere on the board
TGT_SWCLK: CON1.4 (SWCLK), MOD1.5 (SWCLK); also elsewhere on the board
TGT_SWDIO: CON1.2 (SWDIO), MOD1.4 (SWDIO); also elsewhere on the board
TGT_TX: CON1.7 (TGT_TX), MOD1.7 (TGT_TX); also elsewhere on the board
TXD2: MOD1.9 (TX1); also elsewhere on the board
